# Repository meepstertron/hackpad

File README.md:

# Meep's Sliding Hacker pad :D

I have made this because i am frustrated how my kb handles music (it only has louder, quieter) so i wanted a slider like they have in actual studios.

## wowie, how did you make such a cool thingie?
### How?
1. Firstly i downloaded libraries and imported them
2. i added the components i wanted (xiao, neopixels, slider, buttons)
3. i assigned footprints
4. Layed them out on a pcb
5. desgined a case according to dimensions
6. Designed a lid with cutouts for all components
7. Wrote this README

### hows the binarys looking for this project?
I used:
- KiCad - For the pcb
- Fusion 360 - For the case
- Windows (no arch) - As a OS
- HackClub's Hackpad guide - https://hackpad.hackclub.com/guide

## What does it cost (scary)

Estimate: 20-30chf

### BOM (like a reciept)
| ID | Designator                                       | Footprint                                      | Quantity | Designation           | Supplier and Ref |
|----|--------------------------------------------------|------------------------------------------------|----------|------------------------|------------------|
| 1  | D7, D2, D5, D3, D8, D1, D10, D6, D4, D12, D11, D9 | LED_SK6812MINI_PLCC4_3.5x3.5mm_P1.75mm         | 12       | SK6812MINI             |                  |
| 2  | SW3, SW4, SW1, SW2                               | SW_Cherry_MX_1.00u_PCB                         | 4        | SW_Push                |                  |
| 3  | VR1                                              | Potentiometer_Bourns_PTA6043_Single_Slide     | 1        | PTA6043-2015CPB103     |                  |
| 4  | U1                                               | XIAO-RP2040-DIP                                | 1        | XIAO-RP2040-DIP        |                  |

i present: **Slidey Macropad thingie!!**

## Images:

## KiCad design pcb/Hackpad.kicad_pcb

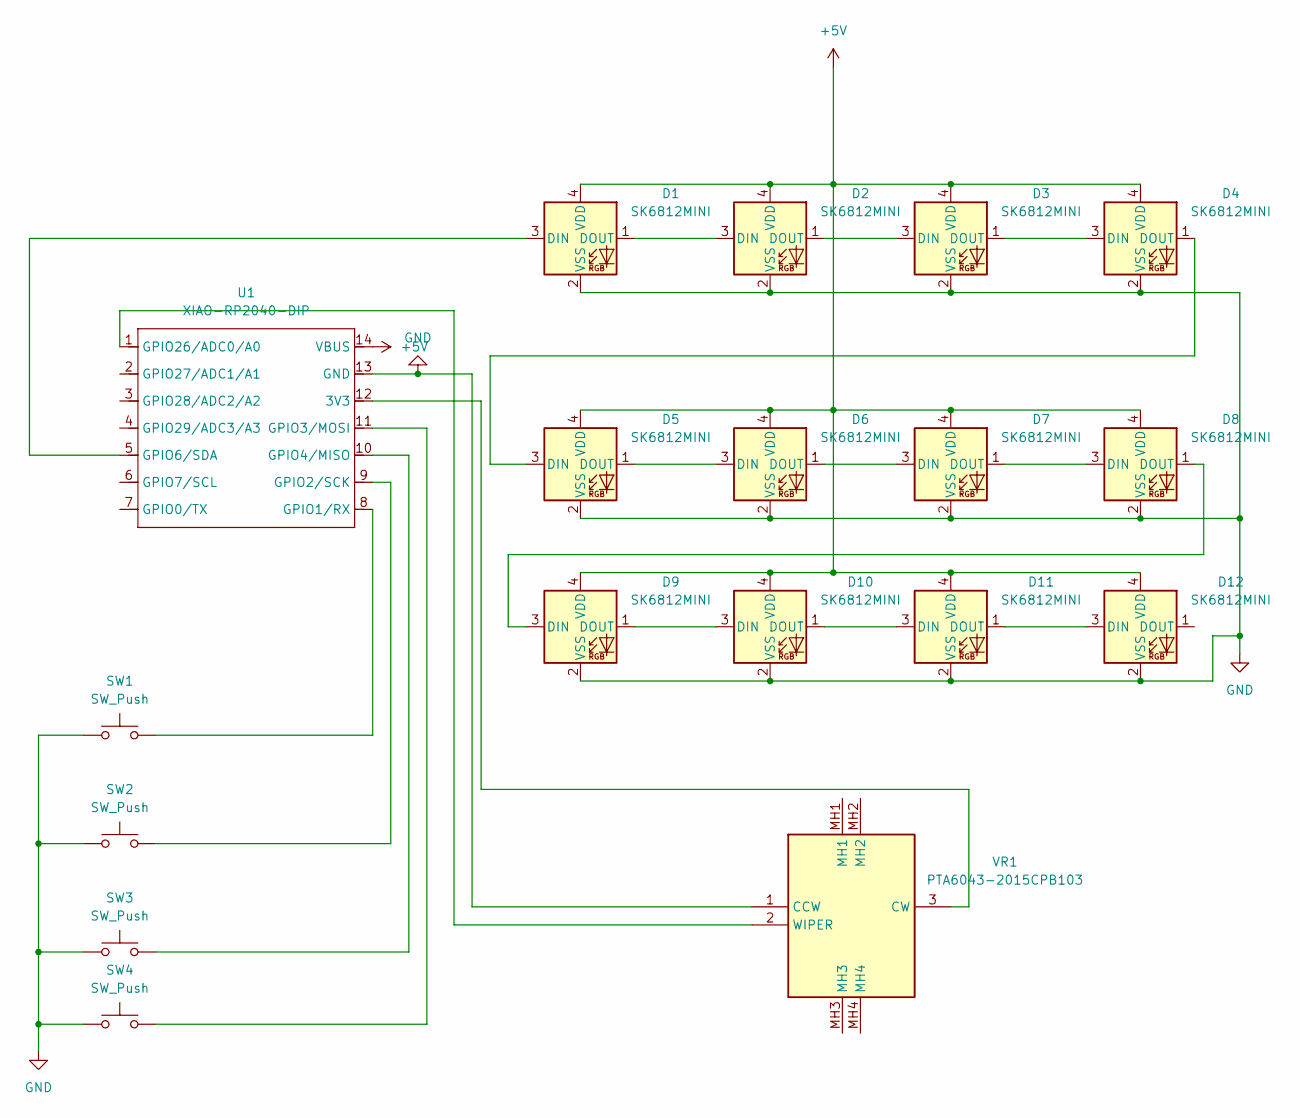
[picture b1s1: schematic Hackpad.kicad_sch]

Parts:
D1, D2, D3, D4, D5, D6, D7, D8, D9, D10, D11, D12: SK6812MINI; LED_SK6812MINI_PLCC4_3.5x3.5mm_P1.75mm
SW1, SW2, SW3, SW4: SW_Push; SW_Cherry_MX_1.00u_PCB
U1: XIAO-RP2040-DIP
VR1: PTA6043-2015CPB103; Potentiometer_Bourns_PTA6043_Single_Slide; Mouser Part Number 652-PTA4432015CPB103

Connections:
+5V: D1.4 (VDD), D2.4 (VDD), D3.4 (VDD), D4.4 (VDD), D5.4 (VDD), D6.4 (VDD), D7.4 (VDD), D8.4 (VDD), D9.4 (VDD), D10.4 (VDD), D11.4 (VDD), D12.4 (VDD), U1.14 (VBUS)
GND: D1.2 (VSS), D2.2 (VSS), D3.2 (VSS), D4.2 (VSS), D5.2 (VSS), D6.2 (VSS), D7.2 (VSS), D8.2 (VSS), D9.2 (VSS), D10.2 (VSS), D11.2 (VSS), D12.2 (VSS), SW1.1, SW2.1, SW3.1, SW4.1, U1.13 (GND), VR1.1 (CCW)
unnamed: D1.3 (DIN), U1.5 (GPIO6/SDA)
unnamed: D1.1 (DOUT), D2.3 (DIN)
unnamed: D2.1 (DOUT), D3.3 (DIN)
unnamed: D3.1 (DOUT), D4.3 (DIN)
unnamed: D4.1 (DOUT), D5.3 (DIN)
unnamed: D5.1 (DOUT), D6.3 (DIN)
unnamed: D6.1 (DOUT), D7.3 (DIN)
unnamed: D7.1 (DOUT), D8.3 (DIN)
unnamed: D8.1 (DOUT), D9.3 (DIN)
unnamed: D9.1 (DOUT), D10.3 (DIN)
unnamed: D10.1 (DOUT), D11.3 (DIN)
unnamed: D11.1 (DOUT), D12.3 (DIN)
unnamed: U1.12 (3V3), VR1.3 (CW)
unnamed: SW1.2, U1.8 (GPIO1/RX)
unnamed: SW2.2, U1.9 (GPIO2/SCK)
unnamed: SW4.2, U1.11 (GPIO3/MOSI)
unnamed: SW3.2, U1.10 (GPIO4/MISO)
unnamed: U1.1 (GPIO26/ADC0/A0), VR1.2 (WIPER)

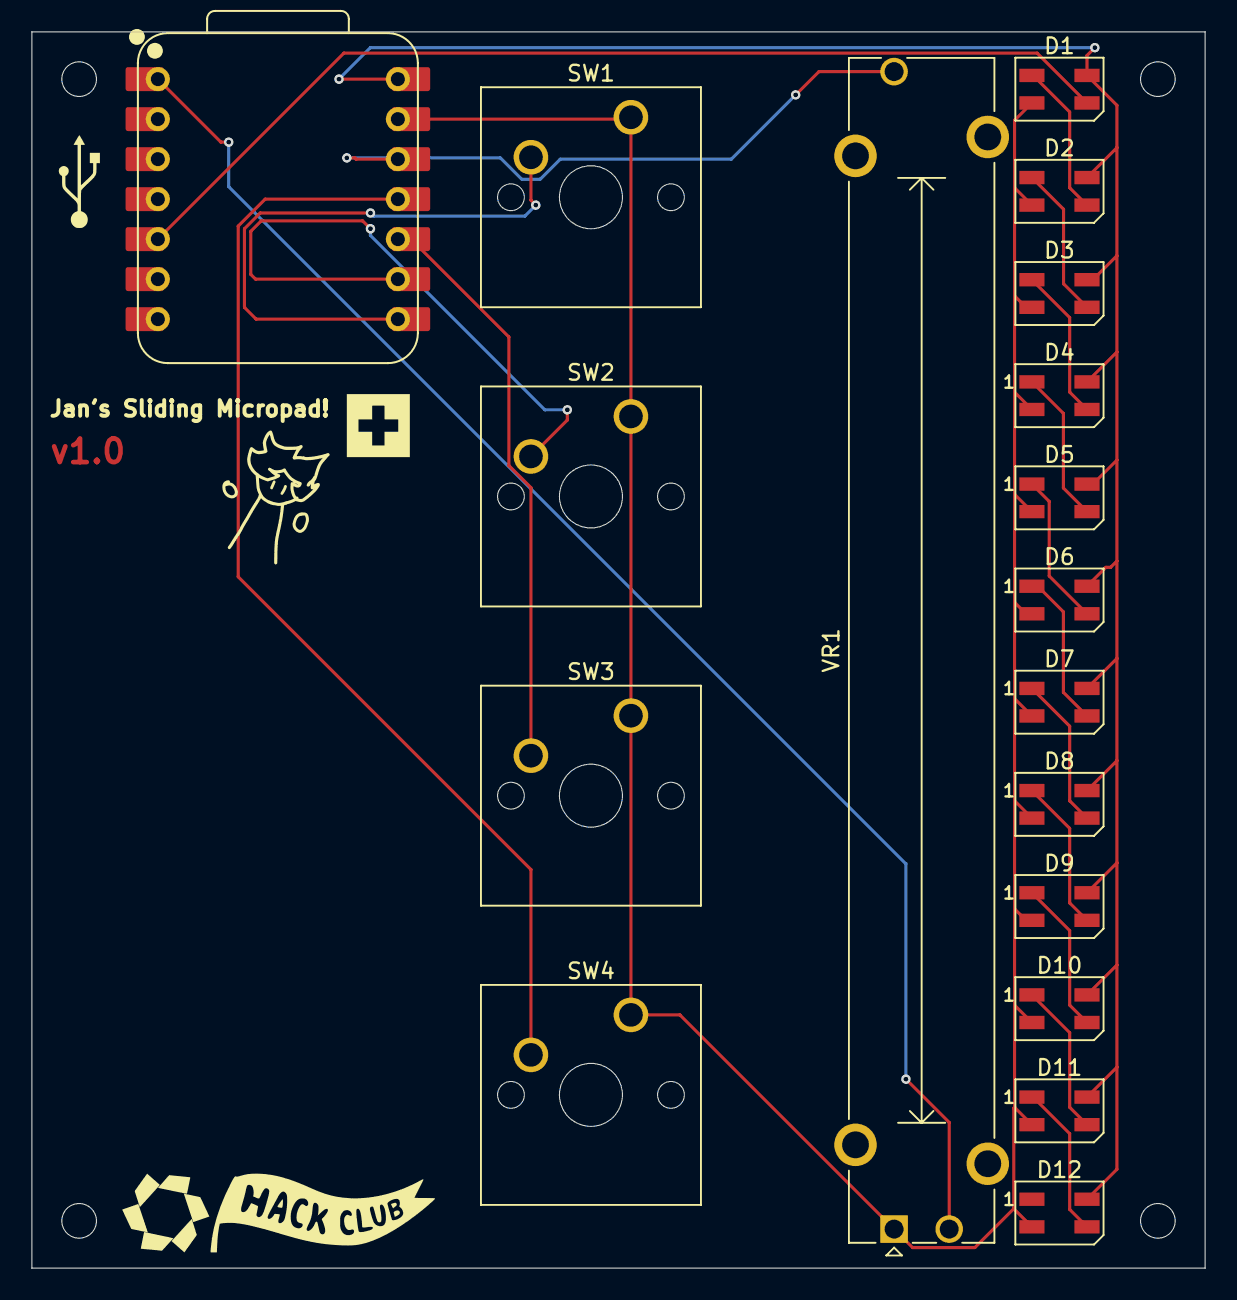
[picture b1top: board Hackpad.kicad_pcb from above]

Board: 2 copper layers, 74.5 x 78.5 mm, 18 parts (0 on the bottom side), 20 nets.

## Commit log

2025-07-10 Added Screenshots
2025-07-10 added more images plus little character :3
2025-07-11 uploaded schematic image
2025-07-11 Folderized the project :D
2025-07-11 refoldered my folders :3
